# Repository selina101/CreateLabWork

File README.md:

# CreateLab work
In this repo you will find all the work done during the master thesis and during the master valorisation (02/2024-12/2024).

For the PCBs, you will find all the KiCAD files, as well as the gerber files to be able to order PCBs. The file 'PCB library' contains the footprint, the symbols and the 3D models of all the components used for all of the PCBs.

## Goat power PCB
Contains the power distribution PCB for Max's robot. 

All the components were bought separately and soldered by hand. 

## Hands
Contains two folders, one with the hall sensors and the other with the FSRs.

For all the Hall sensor PCBs, all the components were bought separately and soldered by hand. 

For the FSRs PCBs, there are no components to solder, one only needs to buy the PCBs and cut the velostat. 

There is a main PCB that allows for connections. On this PCB, 1206 10kOhm pullup resistors are used, and need to be soldered by hand. If the electrodes are used for a hydrogel, a Adafruit ADS7830 Breakout board is needed. 

## IMU
The IMU folder contains various versions of the IMU. 

IMU_V2 is the round PCB that is used for the squid/tentacle projects. They are also the PCBs that need to be mounted on Max's PCB.

IMU_V3 is the sets of PCBs designed for the Helix type robot. There is the main PCBs that has the space for 2 perpendicular IMUs, the teensy and the I2C Qwiic connectors. There are also the files for the rectangular IMUs. 

Both types are accompanied by a pdf explaining everything needed to know for the IMUs. 

The IMUs are bought with the top side soldered on by JLCPCB. They have recently changed there classification of these sensors, so they must be bought in larger quantities and in panels because the PCBs are too small otherwise. The minimum quantity for the V3 was 45 IMUs. The back side of the PCBs must then be soldered by hand. 
For the main PCB, all the components were bought separately and soldered by hand.

## MPXH6115AC6U_breakout
Contains the files for the PCBs that Kai asked for, it is a breakout for the MPXH6115AC6U pressure sensor.

## Tongue
Contains the files for Benhui's Tongue PCB. 

All the components were bought separately and soldered by hand.

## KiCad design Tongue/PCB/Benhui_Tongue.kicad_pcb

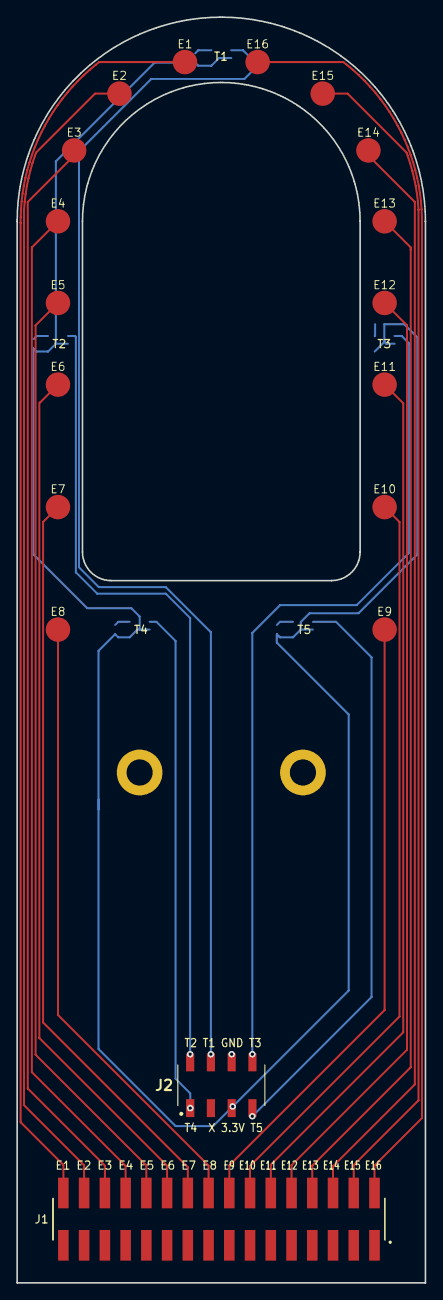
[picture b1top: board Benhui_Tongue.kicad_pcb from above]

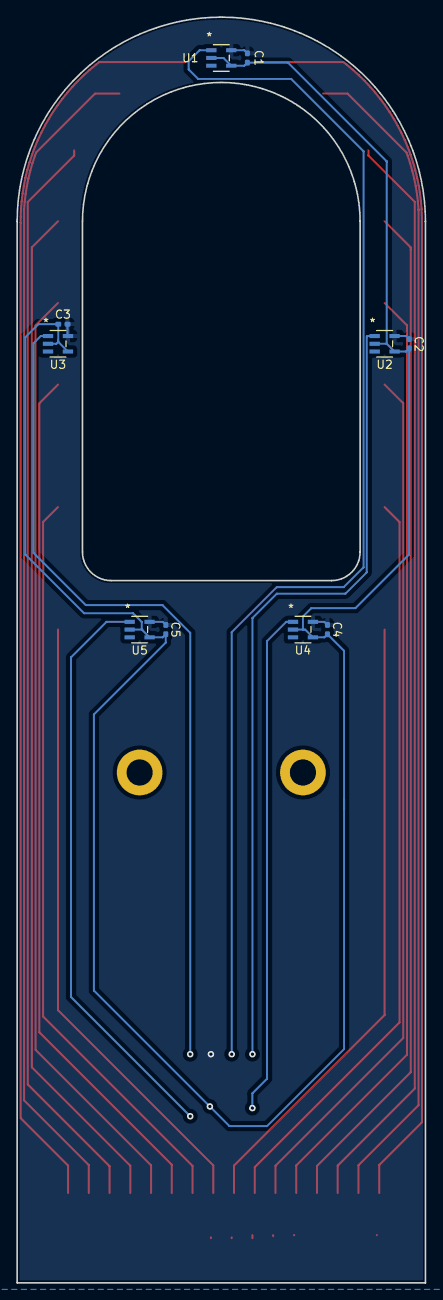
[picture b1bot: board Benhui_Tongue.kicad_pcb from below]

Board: 2 copper layers, 50.0 x 155.0 mm, 30 parts (10 on the bottom side), 23 nets.

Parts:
C1, C2, C3, C4, C5: C; C_0402_1005Metric_Pad0.74x0.62mm_HandSolder
E1, E2, E3, E4, E5, E6, E7, E8, E9, E10, E11, E12, E13, E14, E15, E16: Electrode
H1, H2: MountingHole; MountingHole_3.2mm_M3_DIN965_Pad
J1: SSM-116-L-DV_16x2_FemaleHeader_SMD; SAMTEC_SSM-116-L-DV_16x2_SMD_FemaleHeader
J2: 61030821821_4x2_SMD_FemaleHeader; 61030821821_4x2_FemaleHeader_SMD
U1, U2, U3, U4, U5: TMP37GRTZ-REEL7; TMP37

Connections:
+3.3V: C1.1, C2.1, C3.1, C4.1, C5.1, J2.5, U1.2 (+VS), U1.4 (*SHUTDOWN), U2.2 (+VS), U2.4 (*SHUTDOWN), U3.2 (+VS), U3.4 (*SHUTDOWN), U4.2 (+VS), U4.4 (*SHUTDOWN), U5.2 (+VS), U5.4 (*SHUTDOWN)
/E1: E8.1, J1.18
/E2: E7.1, J1.20
/E3: E6.1, J1.22
/E4: E5.1, J1.24
/E5: E4.1, J1.26
/E6: E3.1, J1.28
/E7: E2.1, J1.30
/E8: E1.1, J1.32
/E9: E16.1, J1.02
/E10: E15.1, J1.04
/E11: E14.1, J1.06
/E12: E13.1, J1.08
/E13: E12.1, J1.10
/E14: E11.1, J1.12
/E15: E10.1, J1.14
/E16: E9.1, J1.16
/T1: J2.4, U1.1 (VOUT)
/T2: J2.2, U2.1 (VOUT)
/T3: J2.8, U3.1 (VOUT)
/T4: J2.1, U4.1 (VOUT)
/T5: J2.7, U5.1 (VOUT)
GND: C1.2, C2.2, C3.2, C4.2, C5.2, J2.6, U1.5 (GND), U2.5 (GND), U3.5 (GND), U4.5 (GND), U5.5 (GND)

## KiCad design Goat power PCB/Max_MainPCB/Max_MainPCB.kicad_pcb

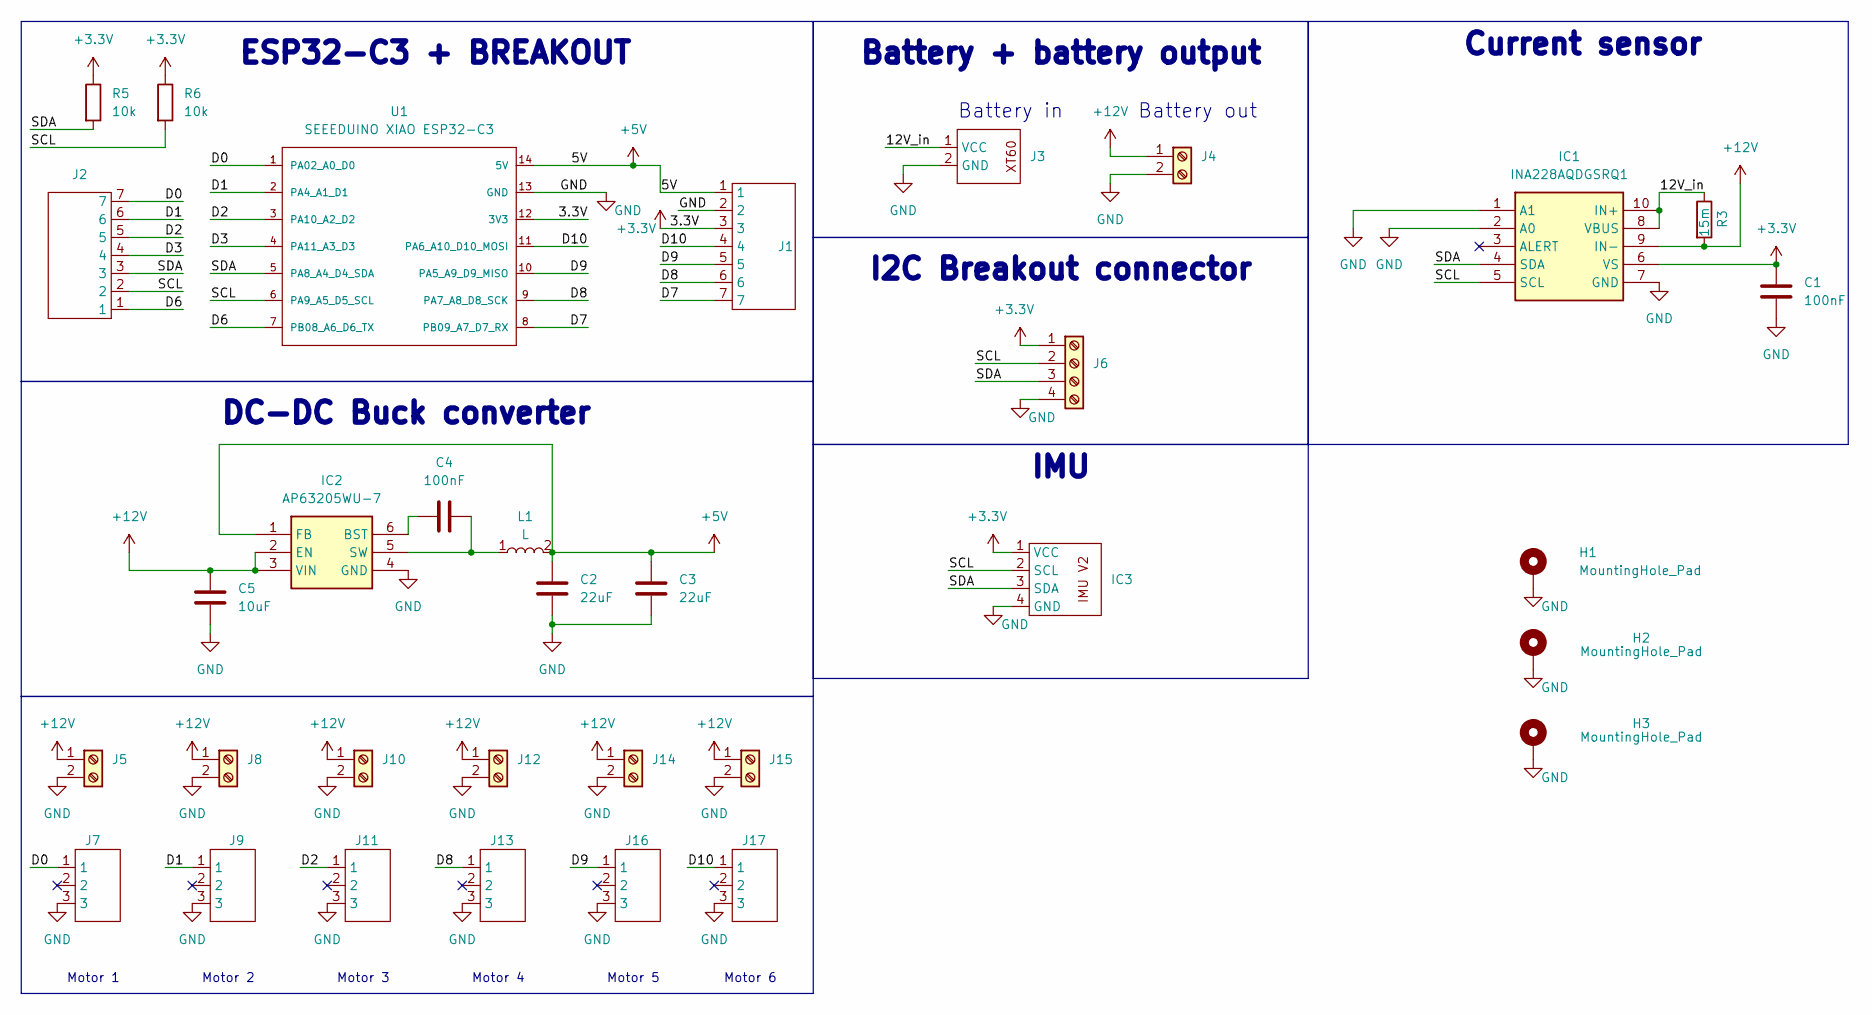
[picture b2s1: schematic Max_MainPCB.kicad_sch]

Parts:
C1, C4: 100nF; C_1206_3216Metric_Pad1.33x1.80mm_HandSolder; LCSC C1945
C2, C3: 22uF; C_1206_3216Metric_Pad1.33x1.80mm_HandSolder; LCSC C77088
C5: 10uF; C_1206_3216Metric_Pad1.33x1.80mm_HandSolder; LCSC C1849
H1, H2, H3: MountingHole_Pad; MountingHole_3.2mm_M3_DIN965_Pad
IC1: INA228AQDGSRQ1; INA228; Manufacturer_Part_Number INA228AQDGSRQ1; Mouser Part Number 595-INA228AQDGSRQ1
IC2: AP63205WU-7; AP63205WU7; Manufacturer_Part_Number AP63205WU-7; Mouser Part Number 621-AP63205WU-7
IC3: IMU_V2
J1, J2: 1x7_Header
J3: XT60
J4, J5, J8, J10, J12, J14, J15: Screw_Terminal_01x02; TerminalBlock_TE_282834-2_1x02_P2.54mm_Horizontal
J6: Screw_Terminal_01x04; TerminalBlock_TE_282834-4_1x04_P2.54mm_Horizontal
J7: 1x3_FemaleHeader
J9, J11, J13, J16, J17: Screw_Terminal_01x03; 1x3_FemaleHeader
L1: L; CLF12555T-4R7N-H; LCSC C43183
R3: 15m; R_2512_6332Metric_Pad1.40x3.35mm_HandSolder; LCSC C5121111
R5, R6: 10k; R_1206_3216Metric_Pad1.30x1.75mm_HandSolder; LCSC C1489
U1: SEEEDUINO XIAO ESP32-C3; Seed Studio XIAO ESP32C3 (with holes)

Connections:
+3.3V: C1.1, IC1.6 (VS), IC3.1 (VCC), J1.3, J6.1, R5.1, R6.1, U1.12 (3V3)
+5V: C2.1, C3.1, IC2.1 (FB), J1.1, L1.2, U1.14 (5V)
+12V: C5.1, IC1.9 (IN-), IC2.2 (EN), IC2.3 (VIN), J4.1, J5.1, J8.1, J10.1, J12.1, J14.1, J15.1, R3.2; also elsewhere on the board
/12V_in: IC1.8 (VBUS), IC1.10 (IN+), J3.1 (VCC), R3.1
/D0: J2.7, J7.1, U1.1 (PA02_A0_D0)
/D1: J2.6, J9.1, U1.2 (PA4_A1_D1)
/D2: J2.5, J11.1, U1.3 (PA10_A2_D2)
/D3: J2.4, U1.4 (PA11_A3_D3)
/D6: J2.1, U1.7 (PB08_A6_D6_TX)
/D7: J1.7, U1.8 (PB09_A7_D7_RX)
/D8: J1.6, J13.1, U1.9 (PA7_A8_D8_SCK)
/D9: J1.5, J16.1, U1.10 (PA5_A9_D9_MISO)
/D10: J1.4, J17.1, U1.11 (PA6_A10_D10_MOSI)
/SCL: IC1.5 (SCL), IC3.2 (SCL), J2.2, J6.2, R6.2, U1.6 (PA9_A5_D5_SCL)
/SDA: IC1.4 (SDA), IC3.3 (SDA), J2.3, J6.3, R5.2, U1.5 (PA8_A4_D4_SDA)
GND: C1.2, C2.2, C3.2, C5.2, H1.1, H2.1, H3.1, IC1.1 (A1), IC1.2 (A0), IC1.7 (GND), IC2.4 (GND), IC3.4 (GND), J1.2, J3.2 (GND), J4.2, J5.2, J6.4, J7.3, J8.2, J9.3, J10.2, J11.3, J12.2, J13.3, J14.2, J15.2, J16.3, J17.3, U1.13 (GND); also elsewhere on the board
unnamed: C4.1, IC2.6 (BST)
unnamed: C4.2, IC2.5 (SW), L1.1

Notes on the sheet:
Current sensor
Battery + battery output
Battery out
Motor 6
ESP32-C3 + BREAKOUT
Battery in
IMU
Motor 2
Motor 4
Motor 3
DC-DC Buck converter
Motor 1
I2C Breakout connector
Motor 5

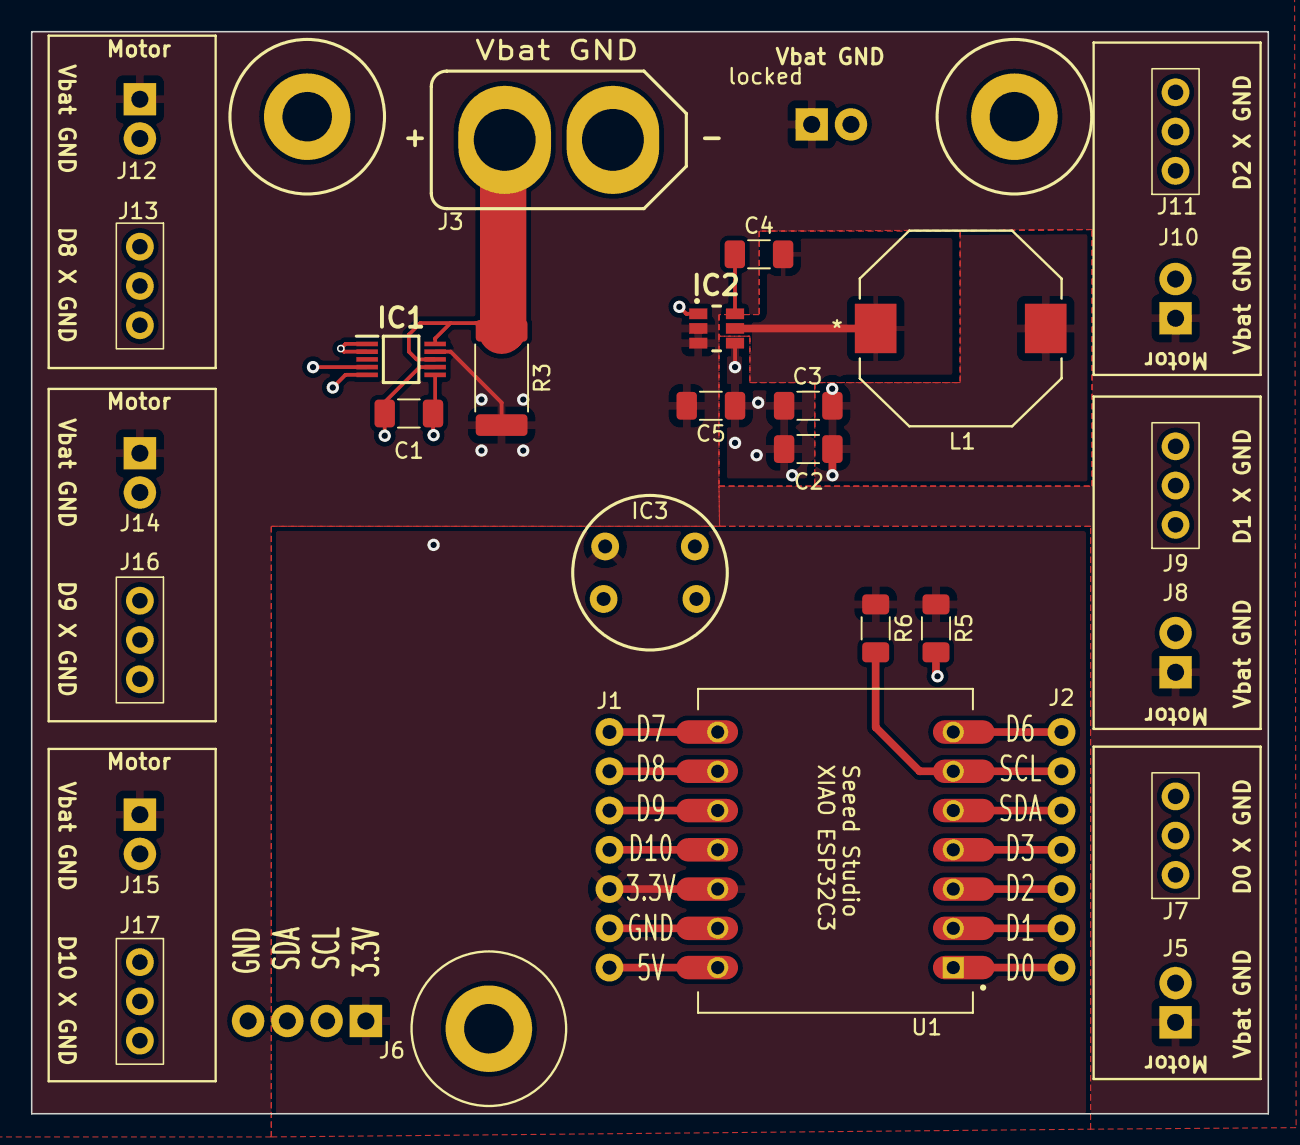
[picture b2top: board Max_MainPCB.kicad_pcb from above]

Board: 4 copper layers, 80.0 x 70.0 mm, 33 parts (0 on the bottom side), 18 nets.

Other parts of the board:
locked: Screw_Terminal_01x02; TerminalBlock_TE_282834-2_1x02_P2.54mm_Horizontal

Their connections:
+12V: locked.1; also elsewhere on the board
GND: locked.2; also elsewhere on the board

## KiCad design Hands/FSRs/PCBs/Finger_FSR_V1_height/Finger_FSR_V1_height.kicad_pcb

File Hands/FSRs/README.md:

# FSR finger sensors

# Code

# PCBs

There are three PCBs for the finger FSRs:
  - The FPCB that has the electrodes in its height. It has the back side in contact with the finger, and the electrodes in contact with the velostat.
  - The FPCB that has the electrodes in its width, and the circular electrodes on the front. The rectangular electrodes are put in contact with the velostat, and the circular electrodes allow for connections to a hydrogel if desired
  - A main PCB that helps connect all these electrodes to a Teensy microcontroller.

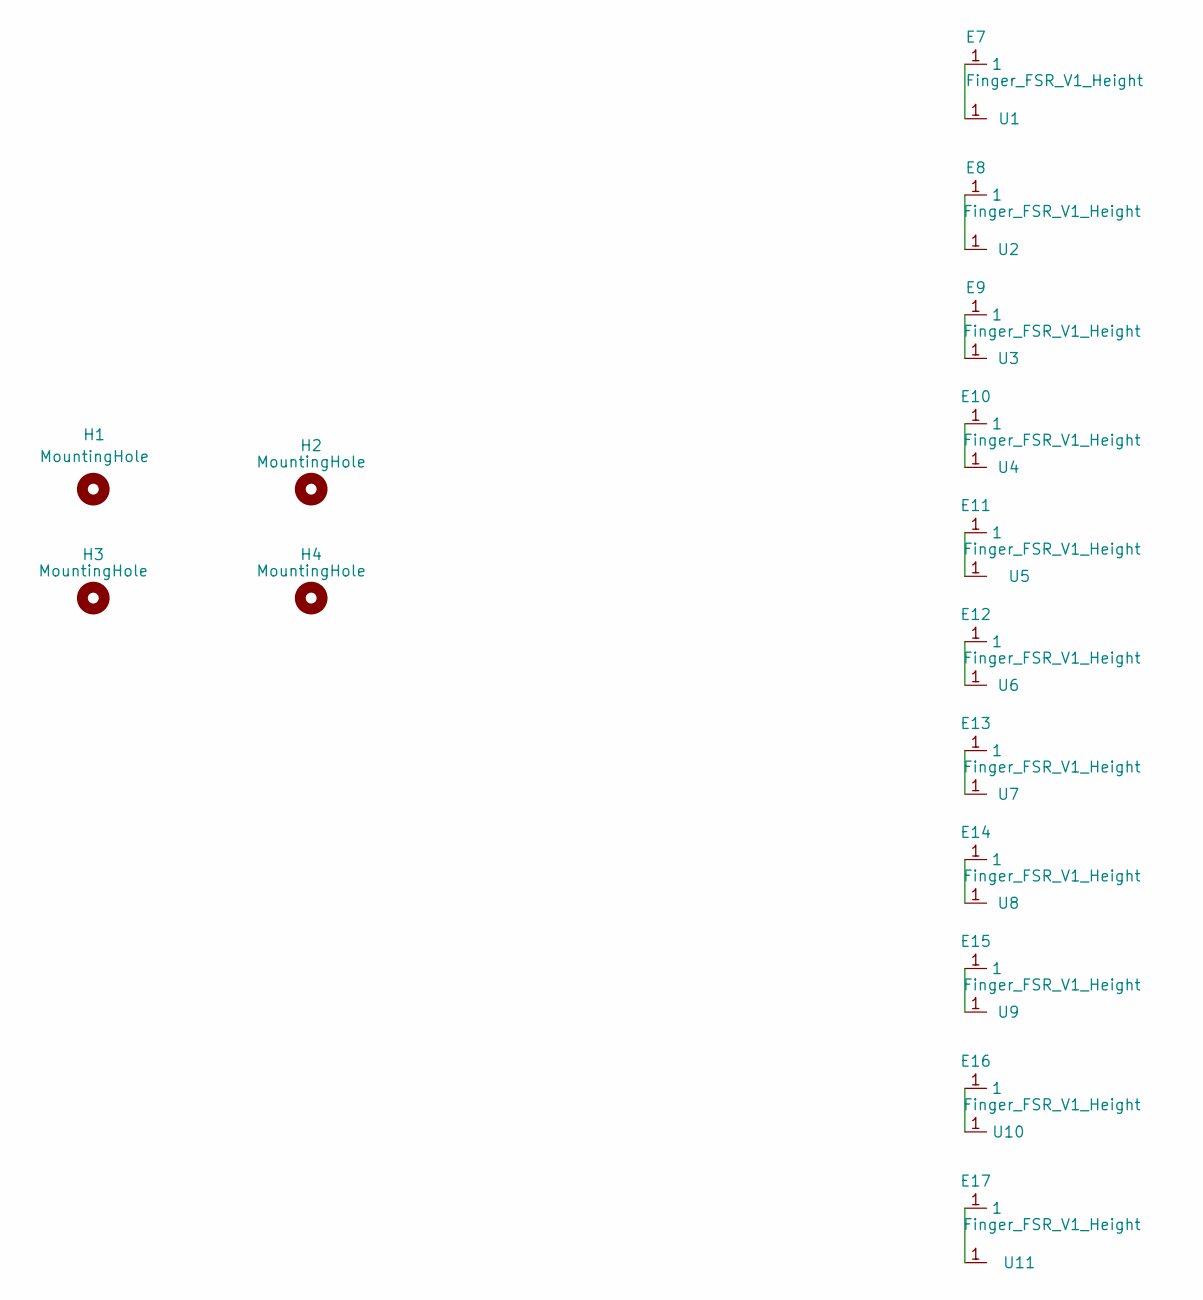
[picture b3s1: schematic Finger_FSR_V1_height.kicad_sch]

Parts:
E7, E8, E9, E10, E11, E12, E13, E14, E15, E16, E17: Finger_FSR_V1_Height
H1, H2, H3, H4: MountingHole; MountingHole_2.2mm_M2_DIN965_Pad
U1, U2, U3, U4, U5, U6, U7, U8, U9, U10, U11: pad; Long_pad

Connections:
unnamed: E7.1, U1.1
unnamed: E8.1, U2.1
unnamed: E9.1, U3.1
unnamed: E10.1, U4.1
unnamed: E11.1, U5.1
unnamed: E12.1, U6.1
unnamed: E13.1, U7.1
unnamed: E14.1, U8.1
unnamed: E15.1, U9.1
unnamed: E16.1, U10.1
unnamed: E17.1, U11.1

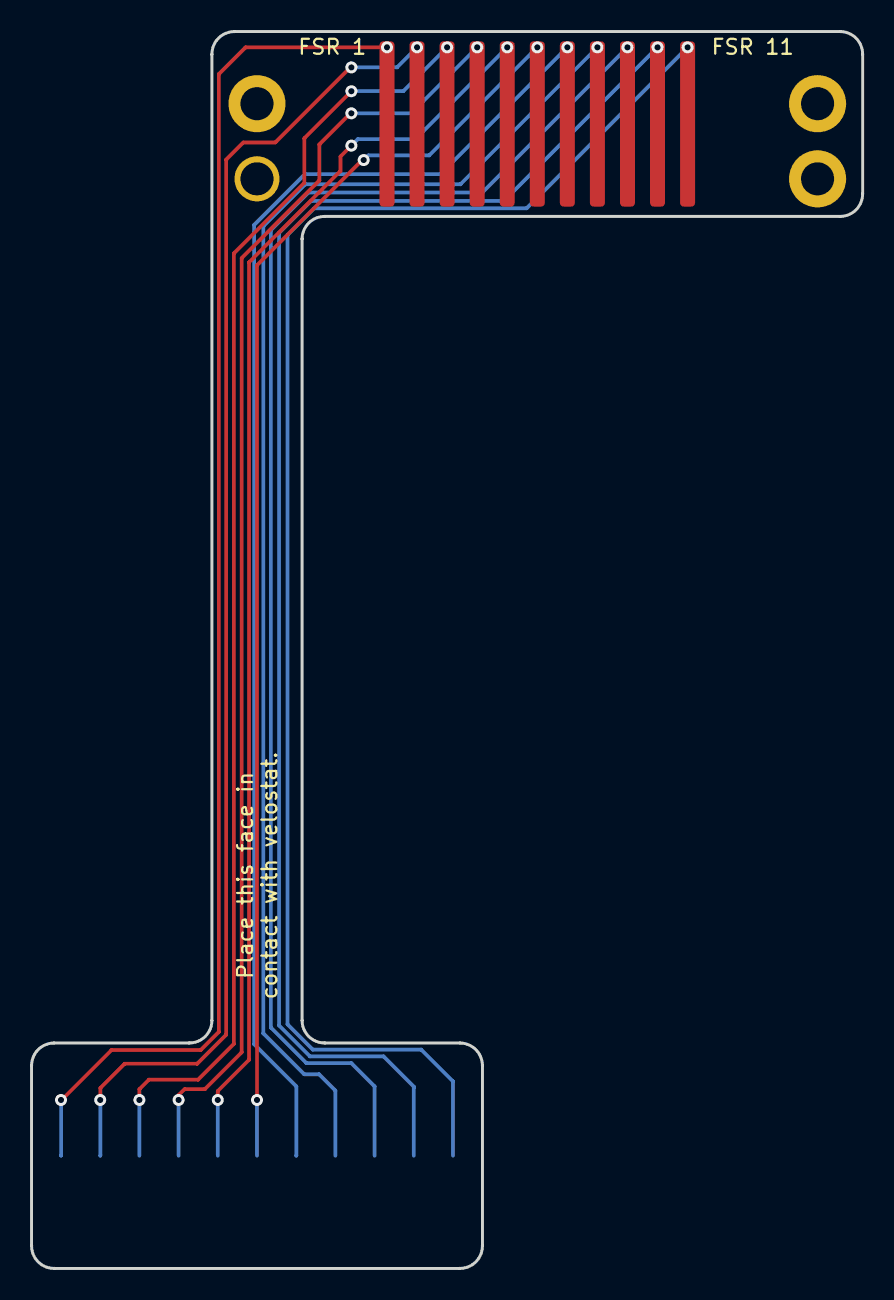
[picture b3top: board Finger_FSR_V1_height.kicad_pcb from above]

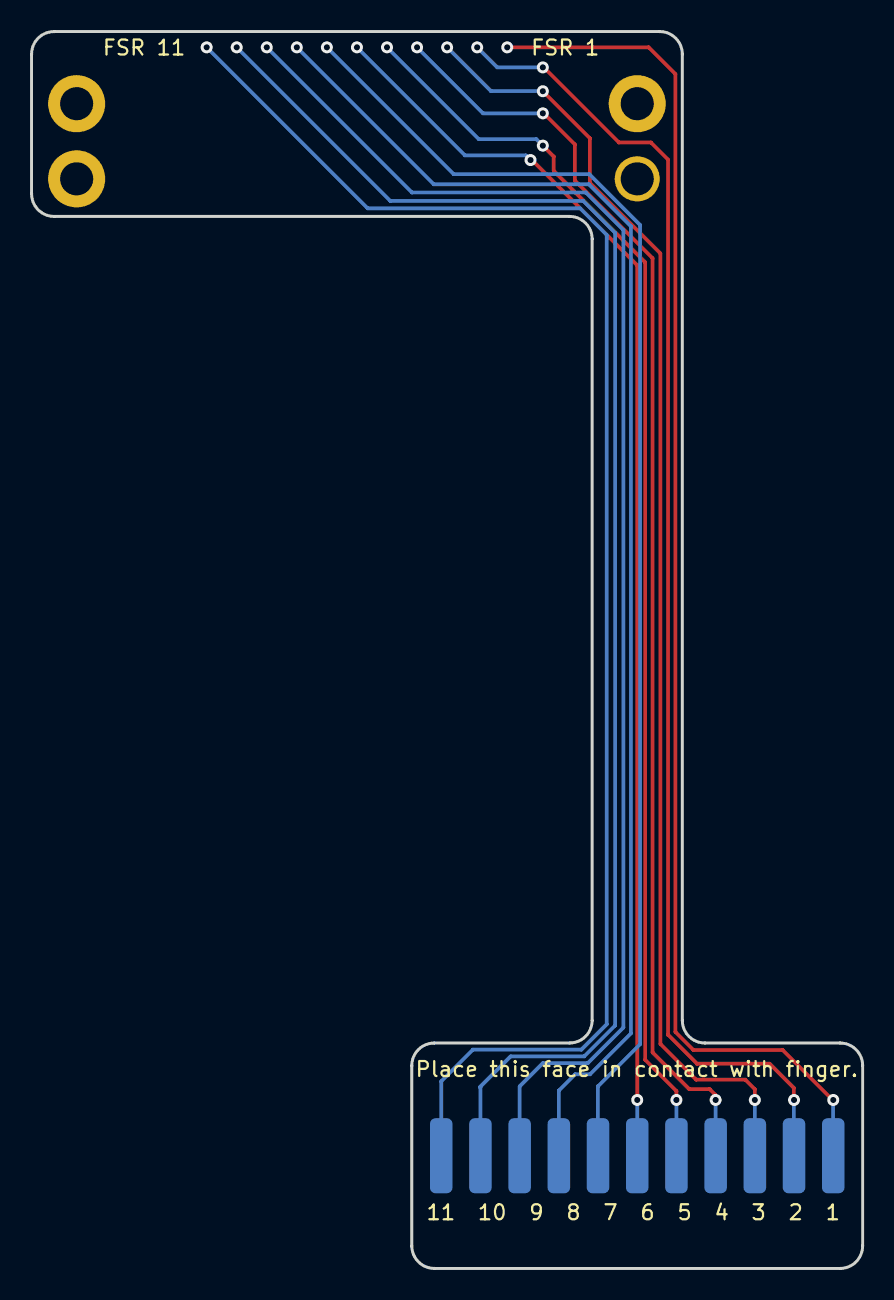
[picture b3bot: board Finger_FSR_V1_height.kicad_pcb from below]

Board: 2 copper layers, 55.3 x 82.3 mm, 26 parts (11 on the bottom side), 11 nets.

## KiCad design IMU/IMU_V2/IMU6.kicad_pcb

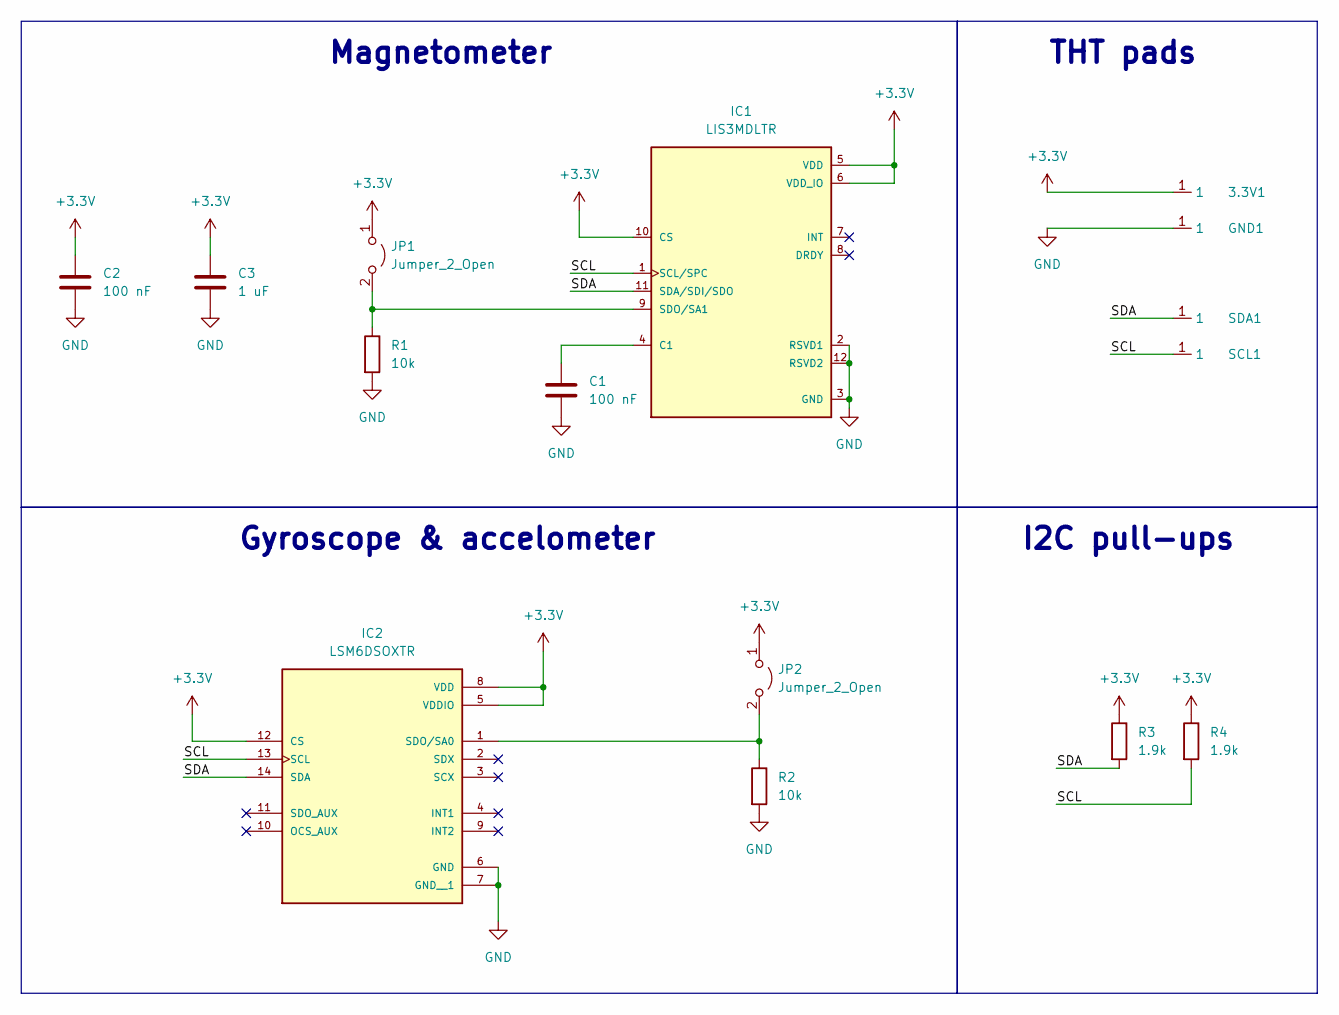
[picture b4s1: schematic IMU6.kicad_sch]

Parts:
3.3V1: THT_Small
C1, C2: 100 nF; C_0402_1005Metric_Pad0.74x0.62mm_HandSolder; LCSC C60474
C3: 1 uF; C_0402_1005Metric_Pad0.74x0.62mm_HandSolder; LCSC C15684
GND1: THT_Small
IC1: LIS3MDLTR; PARTREV 6; LCSC C478483
IC2: LSM6DSOXTR; PARTREV 3.0; LCSC C481766
JP1, JP2: Jumper_2_Open; SolderJumper-2_P1.3mm_Open_Pad1.0x1.5mm
R1, R2: 10k; R_0402_1005Metric_Pad0.72x0.64mm_HandSolder; LCSC C60490
R3, R4: 1.9k; R_0402_1005Metric_Pad0.72x0.64mm_HandSolder; LCSC C60490
SCL1: THT_Small
SDA1: THT_Small

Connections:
+3.3V: 3.3V1.1, C2.1, C3.1, IC1.5 (VDD), IC1.6 (VDD_IO), IC1.10 (CS), IC2.5 (VDDIO), IC2.8 (VDD), IC2.12 (CS), JP1.1 (A), JP2.1 (A), R3.1, R4.1
/SCL: IC1.1 (SCL/SPC), IC2.13 (SCL), R4.2, SCL1.1
/SDA: IC1.11 (SDA/SDI/SDO), IC2.14 (SDA), R3.2, SDA1.1
GND: C1.2, C2.2, C3.2, GND1.1, IC1.2 (RSVD1), IC1.3 (GND), IC1.12 (RSVD2), IC2.6 (GND), IC2.7 (GND__1), R1.2, R2.2
unnamed: C1.1, IC1.4 (C1)
unnamed: IC1.9 (SDO/SA1), JP1.2 (B), R1.1
unnamed: IC2.1 (SDO/SA0), JP2.2 (B), R2.1

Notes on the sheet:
THT pads
I2C pull-ups
Gyroscope & accelometer
Magnetometer

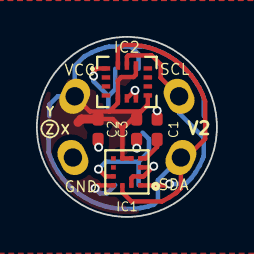
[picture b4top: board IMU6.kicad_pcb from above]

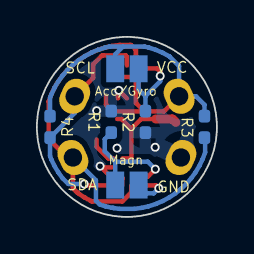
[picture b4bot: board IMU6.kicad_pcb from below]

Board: 2 copper layers, 10.0 x 10.0 mm, 15 parts (6 on the bottom side), 7 nets.

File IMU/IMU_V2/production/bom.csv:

Designator,Footprint,Quantity,Value,LCSC Part #
"3.3V1, GND1, SCL1, SDA1",THT_Small,4,~,
"C1, C2",0402,2,100 nF,C60474
C3,0402,1,1 uF,C15684
IC1,LIS3MDLTR,1,LIS3MDLTR,C478483
IC2,LSM6DSOXTR,1,LSM6DSOXTR,C481766
"JP1, JP2",SolderJumper-2_P1.3mm_Open_Pad1.0x1.5mm,2,Jumper_2_Open,
"R1, R2",0402,2,10k,C60490
"R3, R4",0402,2,1.9k,C60490

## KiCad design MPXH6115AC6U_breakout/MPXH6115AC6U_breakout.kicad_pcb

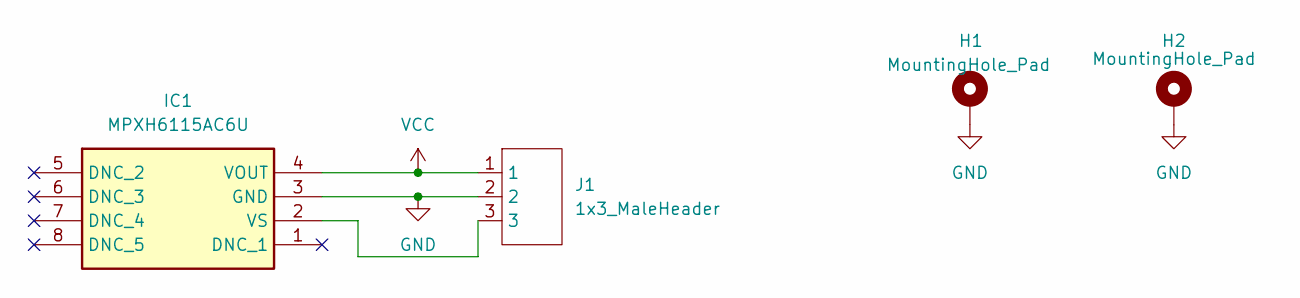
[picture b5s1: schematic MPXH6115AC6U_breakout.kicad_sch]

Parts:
H1, H2: MountingHole_Pad; MountingHole_2.2mm_M2_DIN965_Pad
IC1: MPXH6115AC6U; Manufacturer_Part_Number MPXH6115AC6U
J1: 1x3_MaleHeader

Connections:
GND: H1.1, H2.1, IC1.3 (GND), J1.2
unnamed: IC1.2 (VS), J1.3
VCC: IC1.4 (VOUT), J1.1

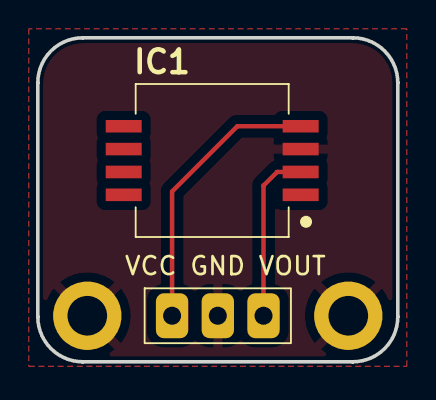
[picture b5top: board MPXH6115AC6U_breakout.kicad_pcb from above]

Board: 2 copper layers, 20.0 x 18.0 mm, 4 parts (0 on the bottom side), 3 nets.

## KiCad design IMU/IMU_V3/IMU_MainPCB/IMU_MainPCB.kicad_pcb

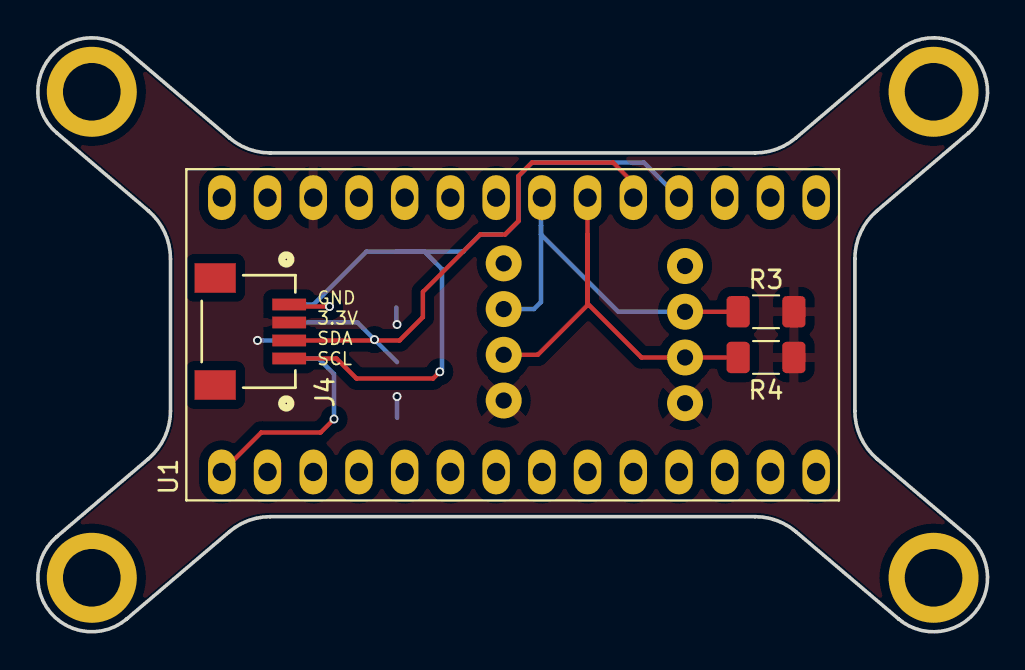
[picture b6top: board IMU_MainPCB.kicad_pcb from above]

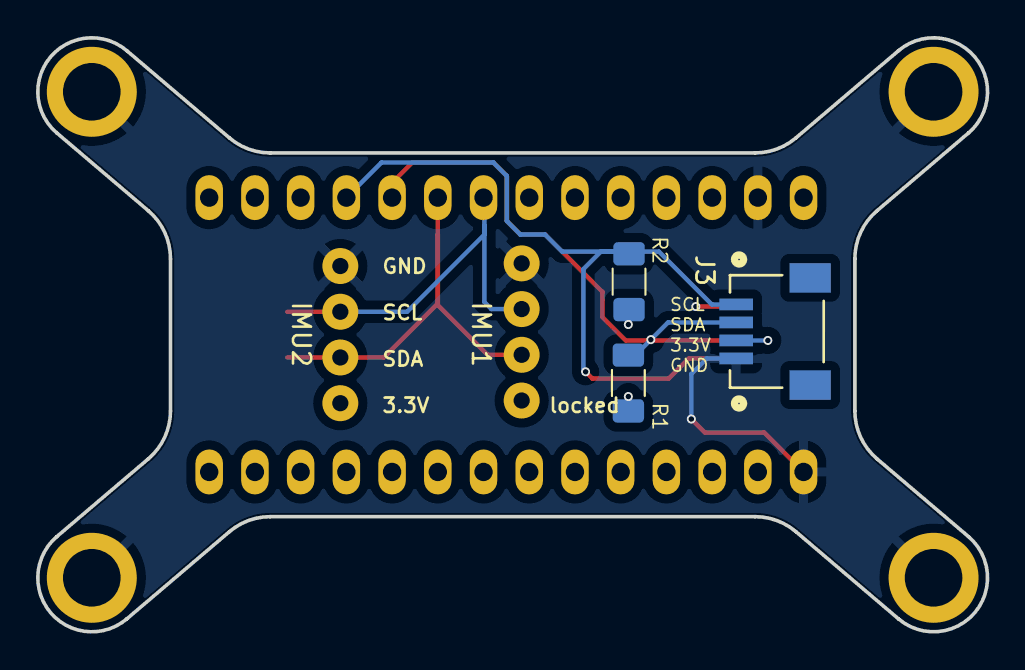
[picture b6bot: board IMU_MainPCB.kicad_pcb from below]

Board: 2 copper layers, 52.8 x 33.0 mm, 13 parts (5 on the bottom side), 6 nets.

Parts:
H1, H2, H3, H4: MountingHole; MountingHole_3.2mm_M3_DIN965_Pad
J1, J2: 4_pin_header; 4 pin header
J3, J4: PRT-14417
R1, R2, R3, R4: R; R_1206_3216Metric_Pad1.30x1.75mm_HandSolder
U1: Teensy_4.0

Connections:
+3.3V: J1.1, J2.1, J3.2, J4.2, R1.1, R2.1, R3.1, R4.1, U1.3.3V_2
/SCL0: J1.3, J2.3, R3.2, U1.19
/SCL1: J3.4, J4.4, R2.2, U1.16
/SDA0: J1.2, J2.2, R4.2, U1.18
/SDA1: J3.3, J4.3, R1.2, U1.17
GND: H1.1, H2.1, H3.1, H4.1, J1.4, J2.4, J3.1, J4.1, U1.G1, U1.G3

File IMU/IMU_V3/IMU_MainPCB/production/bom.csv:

Designator,Footprint,Quantity,Value,LCSC Part #
"H1, H2, H3, H4",MountingHole_3.2mm_M3_DIN965_Pad,4,MountingHole,
"J1, J2",4 pin header,2,4_pin_header,
"J3, J4",PRT-14417,2,~,
"R1, R2, R3, R4",1206,4,R,
U1,Teensy_4.0,1,Teensy_4.0,

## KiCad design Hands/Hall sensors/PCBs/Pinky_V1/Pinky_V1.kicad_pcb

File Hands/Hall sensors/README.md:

# Hand hall sensors

# Code

## To test the PCBs for the full hand:
1) upload the code 'FullHand_HallSensors' to the teensy. This code reads the data of all the sensors and sends it over serial so it can be read in a python script for example. This code does not work with Kai's framework to the full hand, but allows to easily test that all the sensors work correctly. 
2) Run the python code 'FullHand_visualisation' to be able to visualise in python all the sensors of the hand. The area of the circles are proportional to the sensor response.

## To build the PCBs for the full hand:
Upload the code 'FullHand_Haptic_ForAdaptHand' to the teensy. This codes collects the data for all the sensors. This makes is the code needed to connect the PCBs to Kai's framework for the full hand. 

## Arduino code description
- FullHand_HallSensors : This code reads the data of all the sensors and sends it over serial so it can be read in a python script for example.
- FullHand_Haptic : does the same as the 'FullHand_HallSensors' code (reads all the sensor data and sends it over serial) but has in addition the haptic feedback. It controls 5 vibration motor based on the tip sensor values.
-  FullHand_Haptic_ForAdaptHand : Reads all the sensor values. It is compatible with Kai's full hand framework.
-  SingleFinger_withSpringHallSensor : Code for the single finger setup. Reads the 7 hall sensor data + the hall sensor for the spring and sends the data over serial.

## Python code description
- FullHand_tip_visualisation : receives data via serial from the teensy (running the 'FullHand_HallSensors' or 'FullHand_Haptic' code) and displays circles whose area is proportional to the sensor readings. Works only with the tip sensors.
- FullHand_visualisation : receives data via serial from the teensy (running the 'FullHand_HallSensors' or 'FullHand_Haptic' code) and displays circles whose area is proportional to the sensor readings. Works for all the sensors. 

# PCBs
In MainPCB_V3, do not use the DMP31D0U-7 MOSFET but instead use the BSS84. The teensy is not capable of delivering enough current to drive the DMP31D0U-7 gate. 

For each hand, you will need one Thumb_V1 FPCB, three Index_Middle_Ring_V3 FPCB, one Pinky_V1 and one MainPCB_V3. 

The hall sensors exist in three versions (with three different I2C addresses). The correct sensor placement is shown in 'FullHandDiagram.png'.

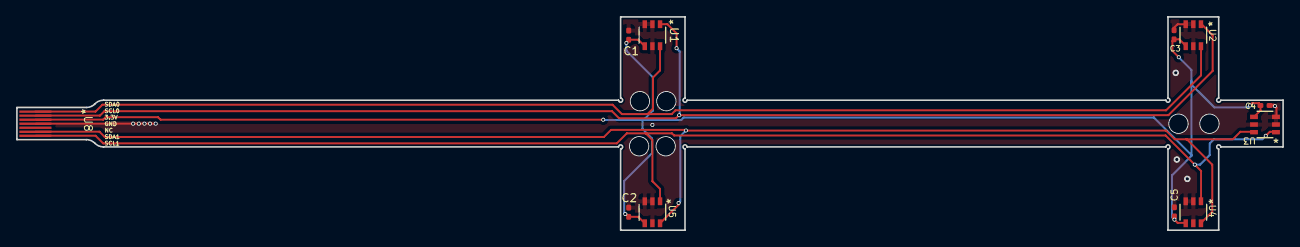
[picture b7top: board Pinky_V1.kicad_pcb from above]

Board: 2 copper layers, 157.3 x 26.5 mm, 11 parts (0 on the bottom side), 6 nets.

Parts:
C1, C2, C3, C4, C5: 0.1uF; C_0402_1005Metric_Pad0.74x0.62mm_HandSolder
U1, U2, U3, U4, U5: TMAG5273A2QDBVR; TMAG5273A2
U8: 7Pin_FingerConnector_for 0527450797

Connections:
+3V3: C1.1, C2.1, C3.1, C4.1, C5.1, U1.4 (VCC), U2.4 (VCC), U3.4 (VCC), U4.4 (VCC), U5.4 (VCC), U8.3
/SCL0: U1.1 (SCL), U2.1 (SCL), U8.2
/SCL1: U3.1 (SCL), U4.1 (SCL), U5.1 (SCL), U8.7
/SDA0: U1.6 (SDA), U2.6 (SDA), U8.1
/SDA1: U3.6 (SDA), U4.6 (SDA), U5.6 (SDA), U8.6
GND: C1.2, C2.2, C3.2, C4.2, C5.2, U1.2 (GND), U1.3 (GND(TEST)), U1.5 (*INT), U2.2 (GND), U2.3 (GND(TEST)), U2.5 (*INT), U3.2 (GND), U3.3 (GND(TEST)), U3.5 (*INT), U4.2 (GND), U4.3 (GND(TEST)), U4.5 (*INT), U5.2 (GND), U5.3 (GND(TEST)), U5.5 (*INT), U8.4

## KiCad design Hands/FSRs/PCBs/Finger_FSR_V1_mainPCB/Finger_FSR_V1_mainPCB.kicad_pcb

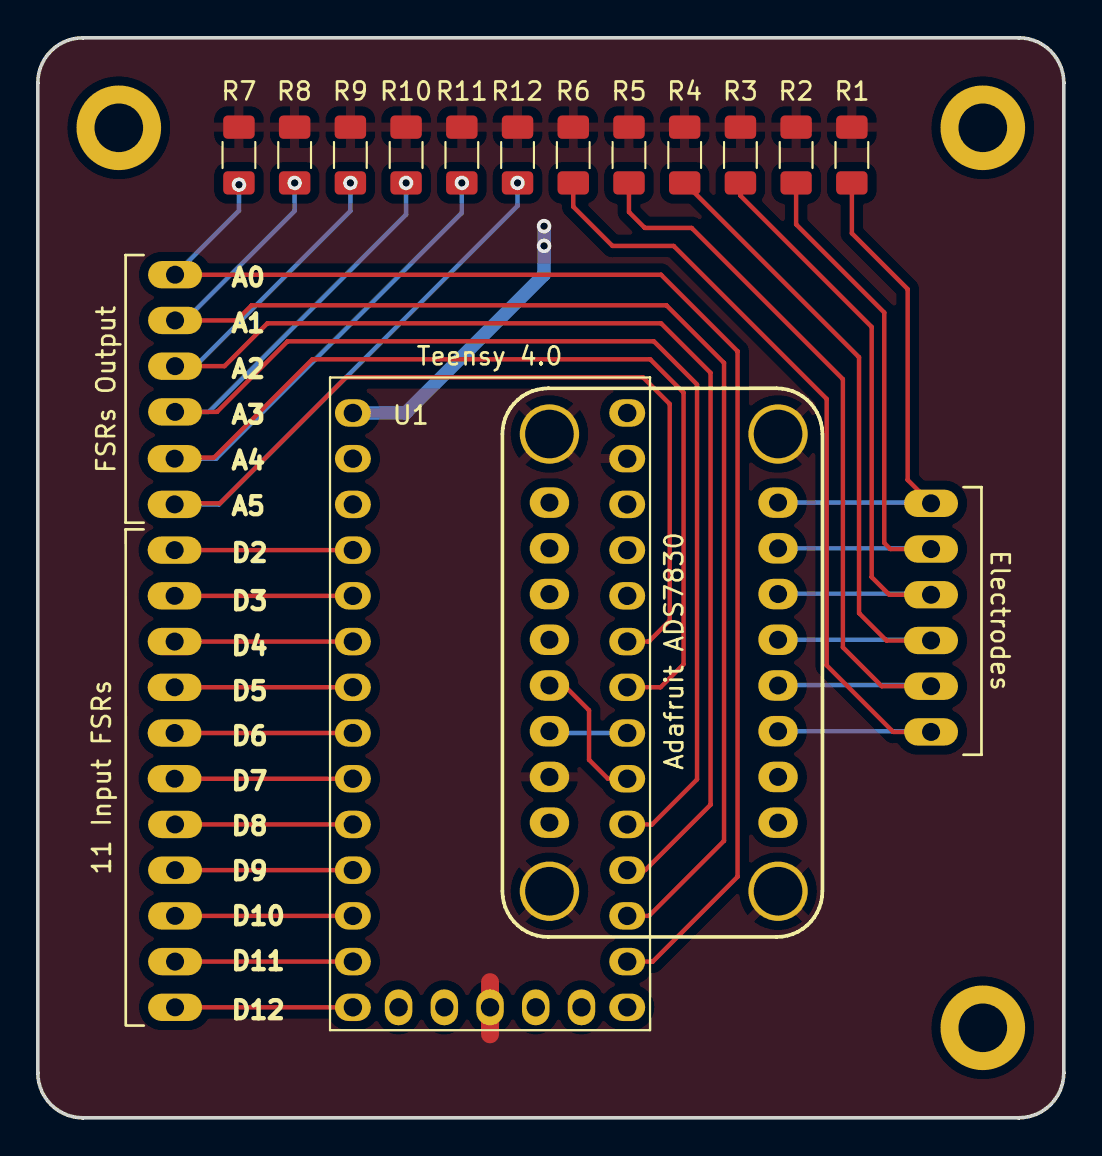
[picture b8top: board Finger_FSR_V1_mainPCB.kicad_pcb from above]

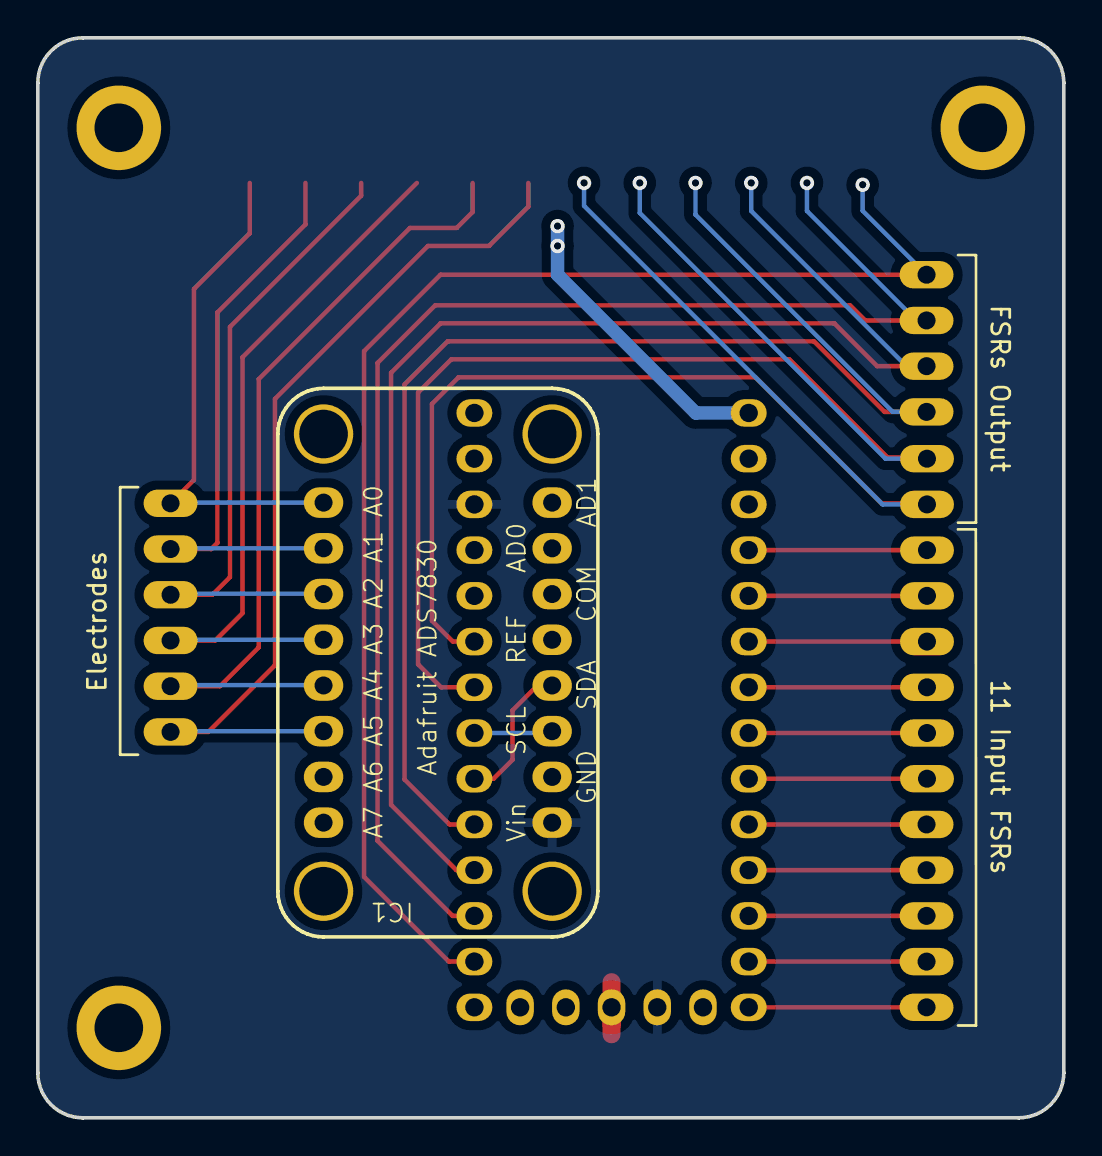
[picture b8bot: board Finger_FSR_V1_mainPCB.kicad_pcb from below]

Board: 2 copper layers, 57.0 x 60.0 mm, 40 parts (7 on the bottom side), 27 nets.

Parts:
H1, H2, H3: MountingHole; MountingHole_2.7mm_M2.5_DIN965_Pad
IC1: Adafruit_ADS7830_Breakout
J1, J2, J3, J4, J5, J6, J7, J8, J9, J10, J11, J12, J13, J14, J15, J16, J17, J18, J19, J20, J21, J22, J23: TH_Pad
R1, R2, R3, R4, R5, R6, R7, R8, R9, R10, R11, R12: R; R_1206_3216Metric_Pad1.30x1.75mm_HandSolder
U1: Teensy_4.0

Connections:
+3.3V: IC1.16 (Vin), U1.3.3V_1, U1.3.3V_2
/A0: IC1.8 (A0), J18.1 (Pad), R1.1
/A1: IC1.7 (A1), J19.1 (Pad), R2.1
/A2: IC1.6 (A2), J20.1 (Pad), R3.1
/A3: IC1.5 (A3), J21.1 (Pad), R4.1
/A4: IC1.4 (A4), J22.1 (Pad), R5.1
/A5: IC1.3 (A5), J23.1 (Pad), R6.1
/SCL: IC1.14 (SCL), U1.19
/SDA: IC1.13 (SDA), U1.18
/T_A0: J12.1 (Pad), R7.1, U1.14
/T_A1: J13.1 (Pad), R8.1, U1.15
/T_A2: J14.1 (Pad), R9.1, U1.16
/T_A3: J15.1 (Pad), R10.1, U1.17
/T_A6: J17.1 (Pad), R11.1, U1.20
/T_A7: J16.1 (Pad), R12.1, U1.21
GND: IC1.0 (Holes), IC1.15 (GND), R1.2, R2.2, R3.2, R4.2, R5.2, R6.2, R7.2, R8.2, R9.2, R10.2, R11.2, R12.2, U1.G1, U1.G2, U1.G3
unnamed: J1.1 (Pad), U1.2
unnamed: J2.1 (Pad), U1.3
unnamed: J3.1 (Pad), U1.4
unnamed: J4.1 (Pad), U1.5
unnamed: J5.1 (Pad), U1.6
unnamed: J6.1 (Pad), U1.7
unnamed: J7.1 (Pad), U1.8
unnamed: J8.1 (Pad), U1.9
unnamed: J9.1 (Pad), U1.10
unnamed: J10.1 (Pad), U1.11
unnamed: J11.1 (Pad), U1.12

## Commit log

2024-12-05 upload
    upload of all the PCB files + useful docs
2024-12-06 update IMU
2024-12-09 update files
2024-12-09 file update
2024-12-10 images added
2024-12-10 image update
